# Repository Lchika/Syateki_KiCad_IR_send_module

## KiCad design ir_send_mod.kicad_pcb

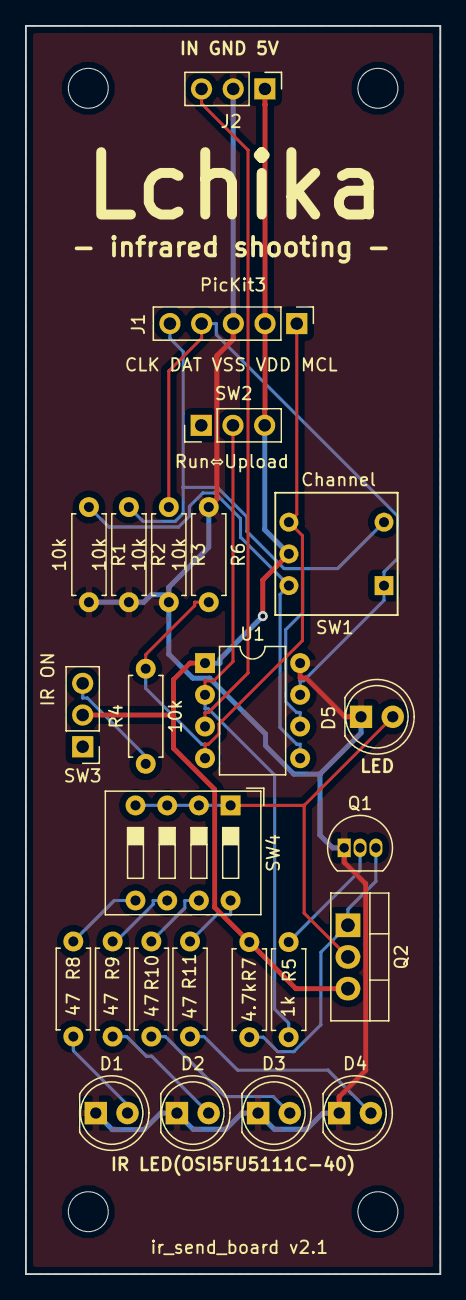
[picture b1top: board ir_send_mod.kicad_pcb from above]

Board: 2 copper layers, 33.2 x 100.0 mm, 29 parts (0 on the bottom side), 20 nets.

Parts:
D1, D2, D3, D4: LED(IR); LED_D5.0mm
D5: LED; LED_D5.0mm
J1: Conn_01x05_Male; PinHeader_1x05_P2.54mm_Vertical
J2: Conn_01x03_Female; PinHeader_1x03_P2.54mm_Vertical
Q1: 2N7000; TO-92_Inline
Q2: IRF9024N; TO-220-3_Vertical
R1, R2, R3, R4, R6: 10k; R_Axial_DIN0207_L6.3mm_D2.5mm_P7.62mm_Horizontal
R5: 1k; R_Axial_DIN0207_L6.3mm_D2.5mm_P7.62mm_Horizontal
R7: 4.7k; R_Axial_DIN0207_L6.3mm_D2.5mm_P7.62mm_Horizontal
R8, R9, R10, R11: 47; R_Axial_DIN0207_L6.3mm_D2.5mm_P7.62mm_Horizontal
SW1: SW_Coded_SH-7040; rotary_sw10
SW2, SW3: SW_SPDT; PinHeader_1x03_P2.54mm_Vertical
SW4: SW_DIP_x04; SW_DIP_SPSTx04_Slide_9.78x12.34mm_W7.62mm_P2.54mm
U1: PIC12F629-IP; DIP-8_W7.62mm
hole1, hole2, hole3, hole4: MountingHole_3.2mm_M3

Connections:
5V: J1.2, J2.1, Q2.3, R7.1, SW1.C, SW2.3, SW3.2, U1.1
GND: D1.1, D2.1, D3.1, D4.1, D5.1, J1.3, J2.2, Q1.1, R1.2, R2.2, R3.2, R6.1, U1.8
unnamed: D1.2, R8.2
unnamed: D2.2, R9.2
unnamed: D3.2, R10.2
unnamed: D4.2, R11.2
unnamed: D5.2, Q2.2, SW4.1, SW4.2, SW4.3, SW4.4
unnamed: J1.1, R4.2, R6.2, SW1.8, U1.4
unnamed: J1.4, R3.1, SW1.1, U1.7
unnamed: J1.5, R2.1, SW1.2, U1.6
unnamed: J2.3, U1.3
unnamed: Q1.2, R5.1
unnamed: Q1.3, Q2.1, R7.2
unnamed: R1.1, SW1.4, U1.5
unnamed: R4.1, SW3.3
unnamed: R5.2, SW2.2, U1.2
unnamed: R8.1, SW4.5
unnamed: R9.1, SW4.6
unnamed: R10.1, SW4.7
unnamed: R11.1, SW4.8

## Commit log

2019-10-05 Update: fix pcb size
